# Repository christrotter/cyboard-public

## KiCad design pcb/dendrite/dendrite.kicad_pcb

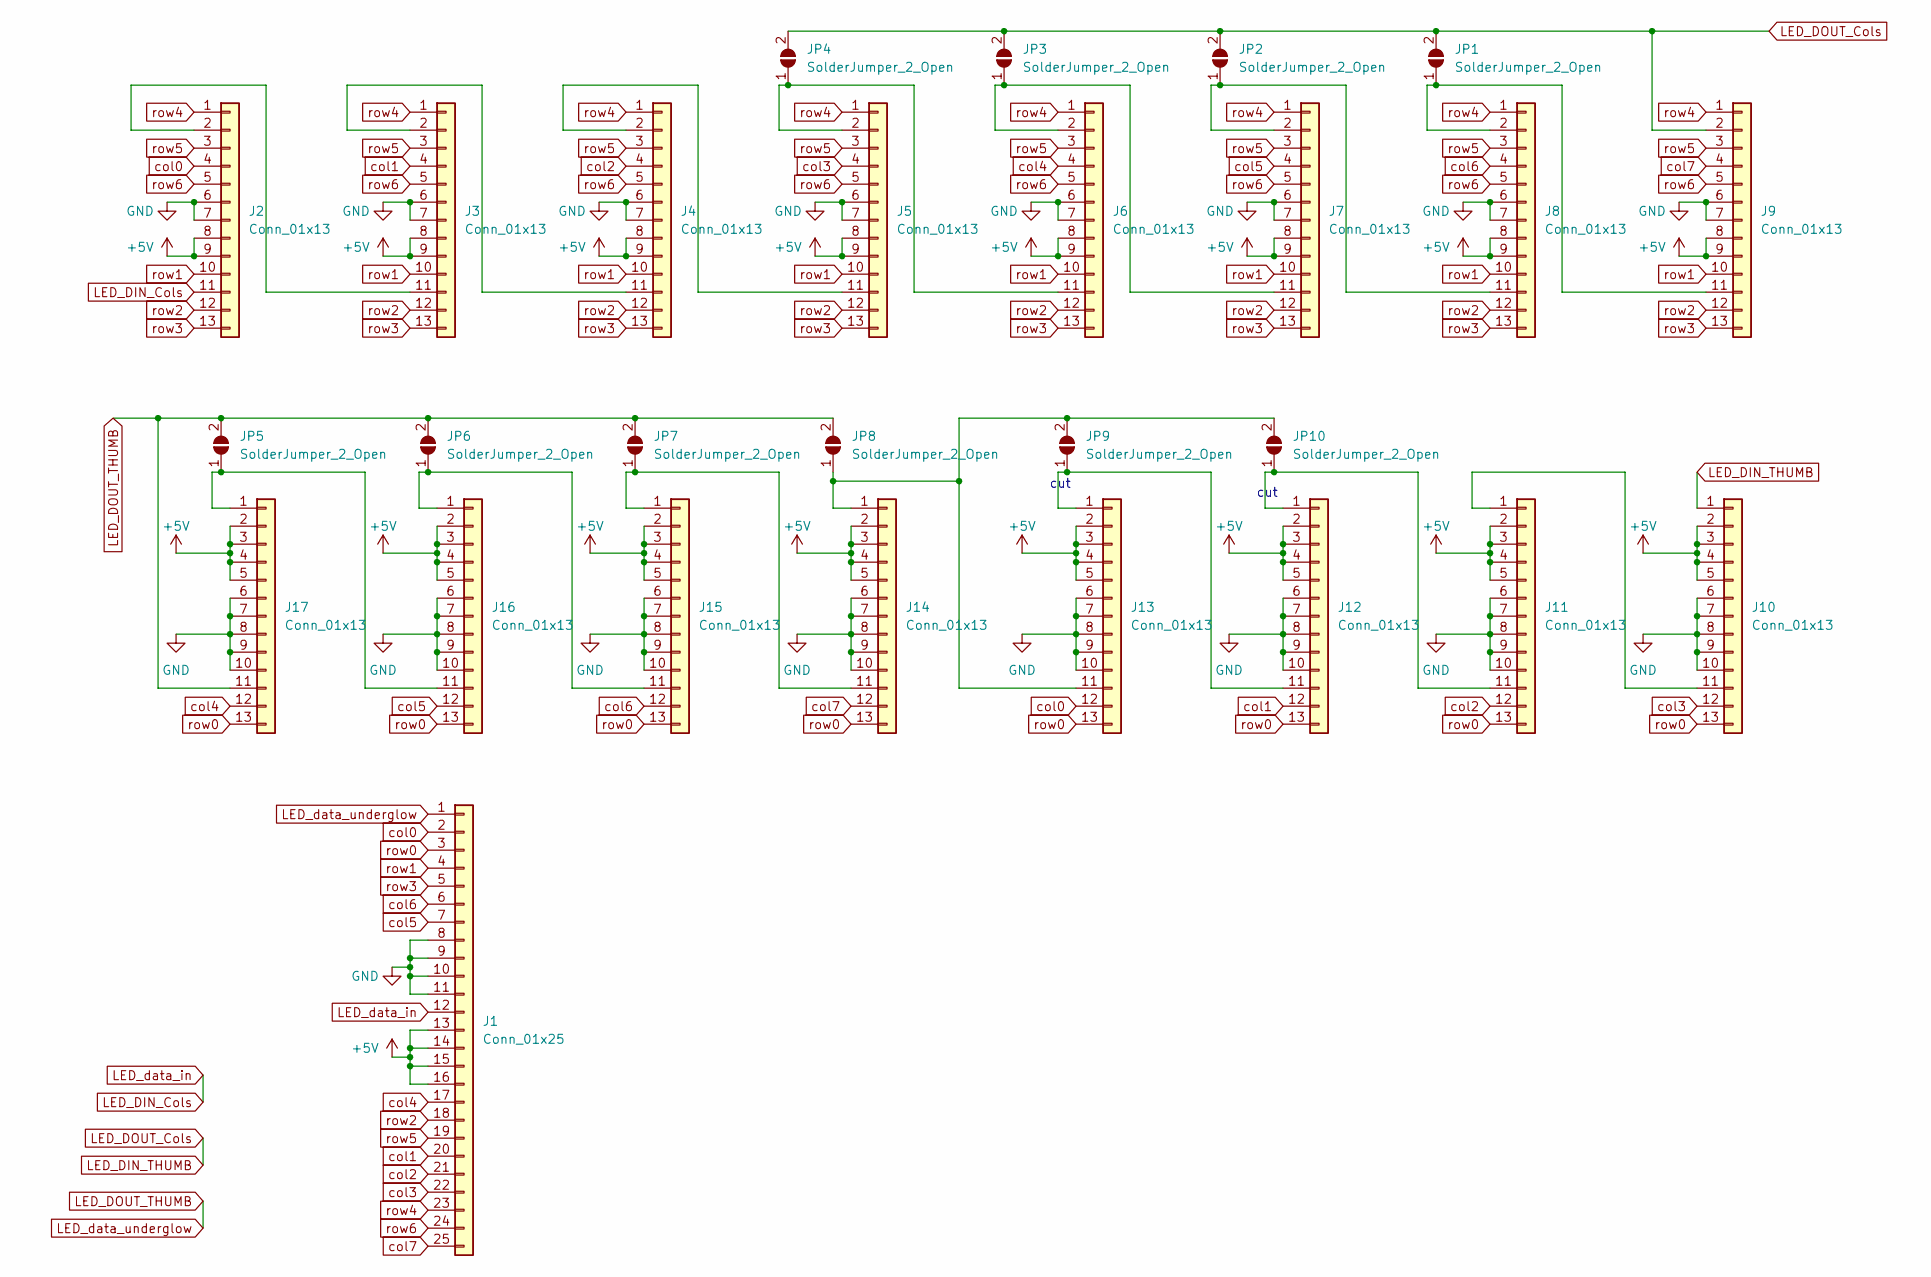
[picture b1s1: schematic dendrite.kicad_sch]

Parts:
J1: Conn_01x25; FFC Termination 25x0.3 ECT818001569
J2, J3, J4, J5, J6, J7, J8, J9, J10, J11, J12, J13, J14, J15, J16, J17: Conn_01x13; FFC Termination 13x0.3 ECT818001568
JP1, JP2, JP3, JP4, JP5, JP6, JP7, JP8, JP9, JP10: SolderJumper_2_Open; SolderJumper-2_P1.3mm_Open_RoundedPad1.0x1.5mm

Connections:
+5V: J1.13, J1.14, J1.15, J1.16, J2.8, J2.9, J3.8, J3.9, J4.8, J4.9, J5.8, J5.9, J6.8, J6.9, J7.8, J7.9, J8.8, J8.9, J9.8, J9.9, J10.2, J10.3, J10.4, J10.5, J11.2, J11.3, J11.4, J11.5, J12.2, J12.3, J12.4, J12.5, J13.2, J13.3, J13.4, J13.5, J14.2, J14.3, J14.4, J14.5, J15.2, J15.3, J15.4, J15.5, J16.2, J16.3, J16.4, J16.5, J17.2, J17.3, J17.4, J17.5
GND: J1.8, J1.9, J1.10, J1.11, J2.6, J2.7, J3.6, J3.7, J4.6, J4.7, J5.6, J5.7, J6.6, J6.7, J7.6, J7.7, J8.6, J8.7, J9.6, J9.7, J10.6, J10.7, J10.8, J10.9, J10.10, J11.6, J11.7, J11.8, J11.9, J11.10, J12.6, J12.7, J12.8, J12.9, J12.10, J13.6, J13.7, J13.8, J13.9, J13.10, J14.6, J14.7, J14.8, J14.9, J14.10, J15.6, J15.7, J15.8, J15.9, J15.10, J16.6, J16.7, J16.8, J16.9, J16.10, J17.6, J17.7, J17.8, J17.9, J17.10
LED_DIN_Cols: J1.12, J2.11
LED_DIN_THUMB: J9.2, J10.1, JP1.2 (B), JP2.2 (B), JP3.2 (B), JP4.2 (B)
LED_DOUT_THUMB: J1.1, J17.11, JP5.2 (B), JP6.2 (B), JP7.2 (B), JP8.2 (B)
unnamed: J2.2, J3.11
unnamed: J3.2, J4.11
unnamed: J4.2, J5.11
unnamed: J5.2, J6.11, JP4.1 (A)
unnamed: J6.2, J7.11, JP3.1 (A)
unnamed: J7.2, J8.11, JP2.1 (A)
unnamed: J8.2, J9.11, JP1.1 (A)
unnamed: J10.11, J11.1
unnamed: J11.11, J12.1, JP10.1 (A)
unnamed: J12.11, J13.1, JP9.1 (A)
unnamed: J13.11, J14.1, JP8.1 (A), JP9.2 (B), JP10.2 (B)
unnamed: J14.11, J15.1, JP7.1 (A)
unnamed: J15.11, J16.1, JP6.1 (A)
unnamed: J16.11, J17.1, JP5.1 (A)
col0: J1.2, J2.4, J13.12
col1: J1.20, J3.4, J12.12
col2: J1.21, J4.4, J11.12
col3: J1.22, J5.4, J10.12
col4: J1.17, J6.4, J17.12
col5: J1.7, J7.4, J16.12
col6: J1.6, J8.4, J15.12
col7: J1.25, J9.4, J14.12
row0: J1.3, J10.13, J11.13, J12.13, J13.13, J14.13, J15.13, J16.13, J17.13
row1: J1.4, J2.10, J3.10, J4.10, J5.10, J6.10, J7.10, J8.10, J9.10
row2: J1.18, J2.12, J3.12, J4.12, J5.12, J6.12, J7.12, J8.12, J9.12
row3: J1.5, J2.13, J3.13, J4.13, J5.13, J6.13, J7.13, J8.13, J9.13
row4: J1.23, J2.1, J3.1, J4.1, J5.1, J6.1, J7.1, J8.1, J9.1
row5: J1.19, J2.3, J3.3, J4.3, J5.3, J6.3, J7.3, J8.3, J9.3
row6: J1.24, J2.5, J3.5, J4.5, J5.5, J6.5, J7.5, J8.5, J9.5

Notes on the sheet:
cut

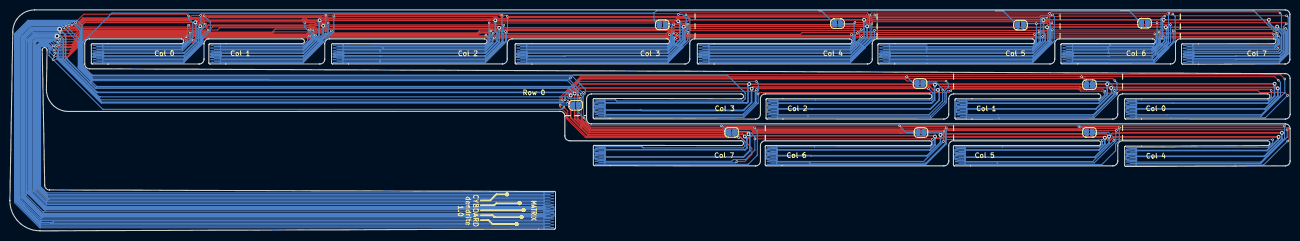
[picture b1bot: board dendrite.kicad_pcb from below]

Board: 2 copper layers, 265.1 x 45.8 mm, 27 parts (10 on the bottom side), 34 nets.

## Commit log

2024-02-20 Add Dendrite 1.0 to open-source files
2024-02-22 extending the cable
